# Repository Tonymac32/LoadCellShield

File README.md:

# LoadCellShield
Dual INA125 Instrumentation Amplifier Shield

This is a 2-channel Instrumentation Amplifier shield based on the Burr-Brown INA125: http://www.ti.com/product/INA125

The purpose of creating it was to monitor 2 load cells at higher speed than possible with the usual sensors, however it can be used to monitor any bridge-based sensor.

Help keep me free to do this sort of thing:
[Donate Here][paypal]

[paypal]: https://www.paypal.com/cgi-bin/webscr?cmd=_s-xclick&hosted_button_id=6JRRCSB28828Y&source=url

## Profile

## Usage

The board was designed for flexibility:  It can power the Arduino, the Arduino (or compatible) can power it.  

U1 offers adequate space for a linear regulator, a DC-DC converter, or a simple jumper in case regulation is not necessary.

Test Points `1..4` and `5..8` are the Vref selection for the two channels.  

TP `9..10` and `11..12` allow for either testing the value of RV1 and RV2 gain potentiometers, or for adding a resistor to set a fixed gain, leaving RV1 and RV2 either unpopulated or swapped for trimming.

Digital I/O 2 and 4 control Channel 0 and Channel 1 amplifier enable, allowing power-down modes

Analog output is presented to Arduino A0 and A1.

## Operating Advisory

The INA125 can operate at high voltages, and can likewise output high voltages.  This design does not currently provide any protection for the Arduino input.

Operating requirements:

* Vin must be higher than the desired Vref.  
    * If Vin is higher than the Arduino-compatible can handle, then a regulator or a dual supply must be used.
    * Higher Vref will result in higher output to the Analog Input of the microcontroller
* Maximum possible output from the amplifier must be within the specification for the Arduino Input.
    * Values vary per board, be certain to check.
    * Reference product page linked above for output characteristics
    
## Tested Configurations (Gain set according to datasheet to be less than max input for boards)

Arduino Uno R3:
* 12V Vin
* Vref 5V
* 3mV/V load cell

Adafruit Metro M4 Express:
* 5V Vin
* Vref 2.5V
* 3mV/V load cell

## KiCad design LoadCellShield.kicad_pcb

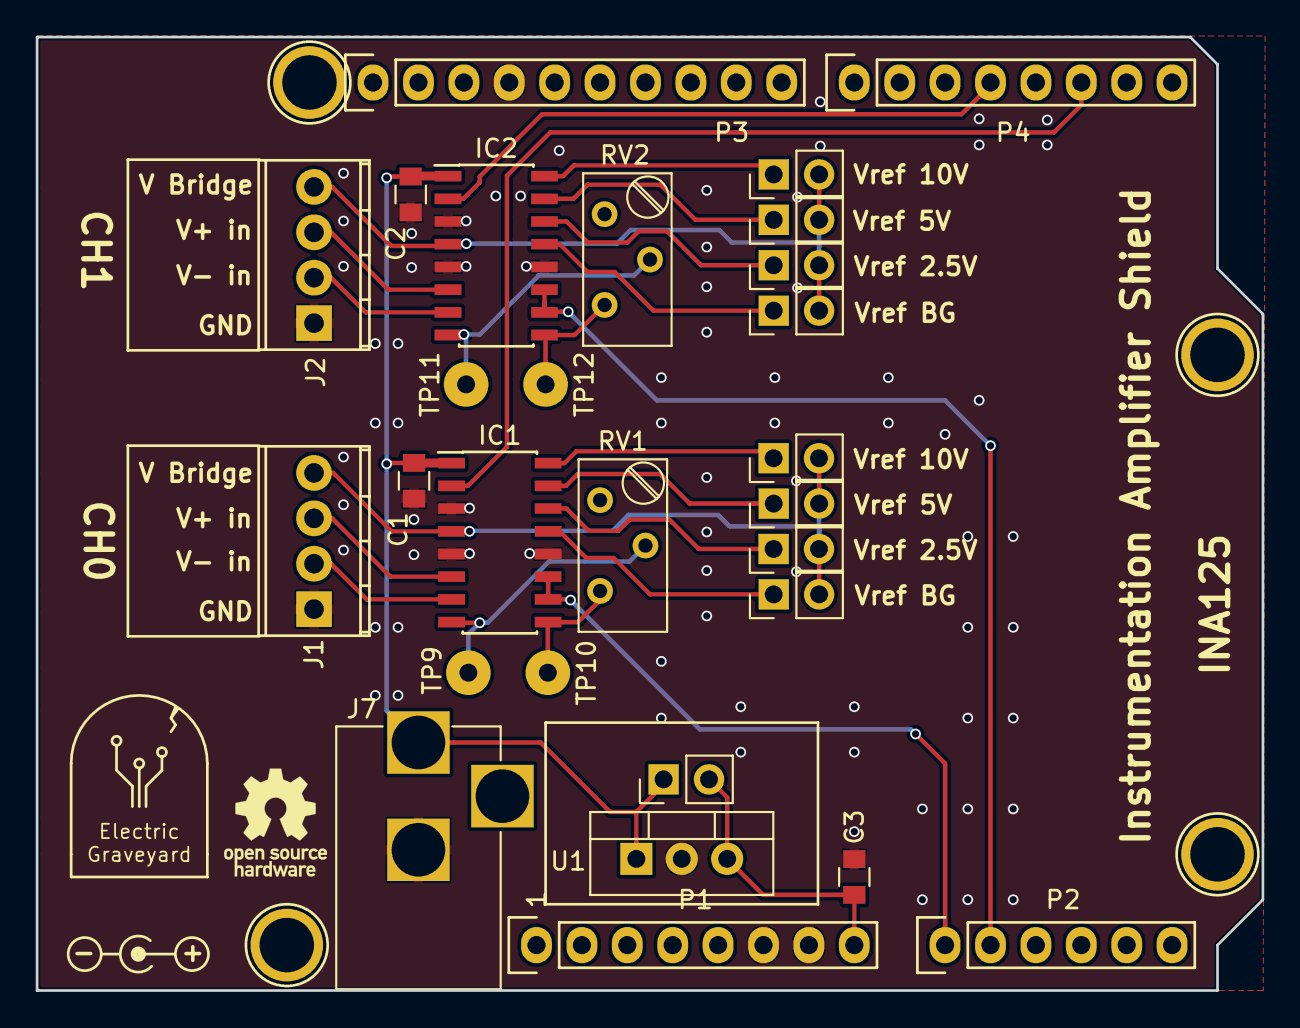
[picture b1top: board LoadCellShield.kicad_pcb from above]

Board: 2 copper layers, 68.6 x 53.3 mm, 31 parts (0 on the bottom side), 27 nets.

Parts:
C1, C2, C3: C; C_0805
IC1, IC2: INA125; SOIC-16_3.9x9.9mm_Pitch1.27mm
J1, J2: Screw_Terminal_01x04; TerminalBlock_Phoenix_MPT-2.54mm_4pol
J7: Barrel_Jack_Switch; BARREL_JACK
P1: Power; Socket_Strip_Arduino_1x08
P2: Analog; Socket_Strip_Arduino_1x06
P3: Digital; Socket_Strip_Arduino_1x10
P4: Digital; Socket_Strip_Arduino_1x08
P5, P6, P7, P8: CONN_01X01; Arduino_1pin
RV1, RV2: R_POT; Potentiometer_Trimmer_Bourns_3296Y
TP1, TP2, TP3, TP4, TP5, TP6, TP7, TP8: TestPoint_2Pole; Pin_Header_Straight_1x02_Pitch2.54mm
TP9, TP10, TP11, TP12: TestPoint; SolderWirePad_single_1mmDrill
U1: R-78E5.0-0.5; TO-220-3_Vertical

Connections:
/A4(SDA): P2.5, P3.2
/A5(SCL): P2.6, P3.1
Analog_Vin: C1.1, C2.1, IC1.1, IC2.1, J7.1, U1.1
Channel0: IC1.10, IC1.11, P2.1
Channel1: IC2.10, IC2.11, P2.2
GND: C1.2, C2.2, C3.2, IC1.3, IC1.5, IC1.12, IC2.3, IC2.5, IC2.12, J1.1, J2.1, J7.2, P1.6, P1.7, P3.4, U1.2
unnamed: IC1.6, J1.3
unnamed: IC1.7, J1.2
unnamed: IC1.8, RV1.2, TP9.1
unnamed: IC1.9, RV1.3, TP10.1
unnamed: IC1.13, TP5.1
unnamed: IC1.14, TP6.1
unnamed: IC1.15, TP7.1
unnamed: IC1.16, TP8.1
unnamed: IC2.6, J2.3
unnamed: IC2.7, J2.2
unnamed: IC2.8, RV2.2, TP11.1
unnamed: IC2.9, RV2.3, TP12.1
unnamed: IC2.13, TP1.1
unnamed: IC2.14, TP2.1
unnamed: IC2.15, TP3.1
unnamed: IC2.16, TP4.1
Sleep0: IC1.2, P4.6
Sleep1: IC2.2, P4.4
V_Bridge0: IC1.4, J1.4, TP5.2, TP6.2, TP7.2, TP8.2
V_Bridge1: IC2.4, J2.4, TP1.2, TP2.2, TP3.2, TP4.2
Vin: C3.1, P1.8, U1.3

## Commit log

2019-01-08 Add board image
    How it looks like.
2019-01-08 add more images for readme
    creating readme content
2019-01-08 Create README.md
    Initial release of readme
2019-01-08 readme typo
2019-01-08 More adjustments
2019-01-08 Create BOM.csv
    Simple reference BOM
2019-01-08 Update BOM.csv
    package sizes
2019-01-08 Update BOM.csv
    formatting fix
2019-01-08 Gerbers
    Gerber files
2019-01-29 Revise Layout to simplify build
    Assembling these was a pain because of the 8x 2 position headers. Squashed them so 2x 8 position ones will work. Also some improvements to general routing.
2019-01-30 Update board-top.png
    update documentation to match routing.
